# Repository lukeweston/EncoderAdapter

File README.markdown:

Differential line driver/converter for position encoders

Differential quadrature output can typically be connected to the servo drive with a four-pair UTP cable - e.g. common Cat. 5 patch cable.
One pair for A, one pair for B, one pair for index and one pair for Vcc/Ground (Vcc = +5V, and the encoder itself also needs to accept 5V).
Power is supplied to the encoder, and the converter board, from the servo drive end.

Copyright Luke Weston, 2015.
Licenced under the CERN Open Hardware Licence v1.2 - see licence subdirectory.

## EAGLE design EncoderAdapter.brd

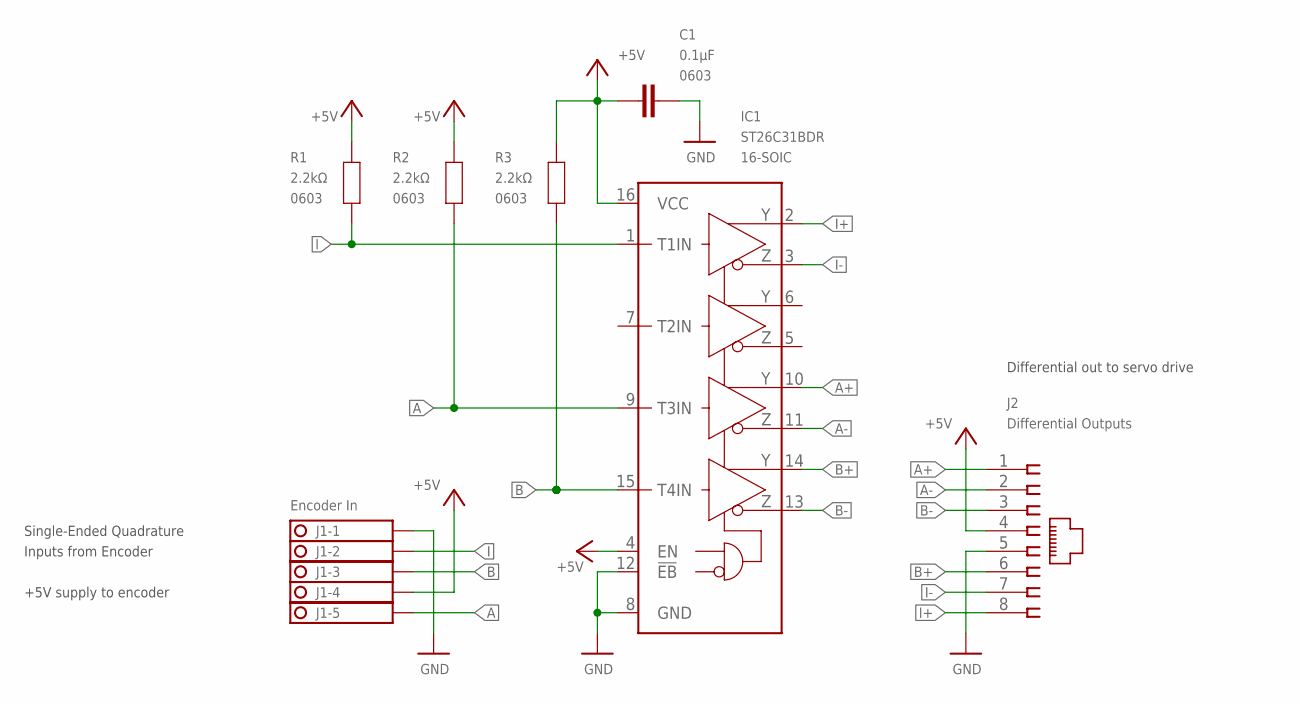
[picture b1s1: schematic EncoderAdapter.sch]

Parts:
C1: 0.1µF; 0603
IC1: ST26C31BDR; SO16
J1: Encoder In; 1751277
J2: Differential Outputs; 215877-4
R1, R2, R3: 2.2kΩ; 0603

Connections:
+5V: C1.2, IC1.4 (EN), IC1.16 (VCC), J1.4, J2.4, R1.1, R2.1, R3.1
A: IC1.9 (T3IN), J1.5, R2.2
A+: IC1.10 (Y3), J2.1
A-: IC1.11 (Z3), J2.2
B: IC1.15 (T4IN), J1.3, R3.2
B+: IC1.14 (Y4), J2.6
B-: IC1.13 (Z4), J2.3
GND: C1.1, IC1.8 (GND), IC1.12 (!EB), J1.1, J2.5
I: IC1.1 (T1IN), J1.2, R1.2
I+: IC1.2 (Y1), J2.8
I-: IC1.3 (Z1), J2.7

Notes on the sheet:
Inputs from Encoder
+5V supply to encoder
Single-Ended Quadrature
Differential out to servo drive

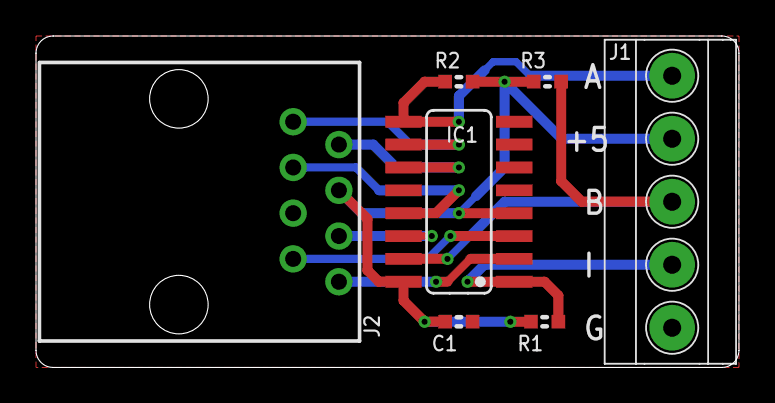
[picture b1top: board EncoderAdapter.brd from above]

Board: 2 copper layers, 39.1 x 18.4 mm, 7 parts (0 on the bottom side), 11 nets.

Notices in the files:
EncoderAdapter.sch:
Copyright (C) Luke Weston, 2015
Open Hardware under the CERN Open Hardware Licence v.1.2.
